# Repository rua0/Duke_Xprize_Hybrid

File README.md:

# Duke_Xprize_Hybrid
Codes and documents for a hybrid-electrical system used for Duke Ocean Xprize entry

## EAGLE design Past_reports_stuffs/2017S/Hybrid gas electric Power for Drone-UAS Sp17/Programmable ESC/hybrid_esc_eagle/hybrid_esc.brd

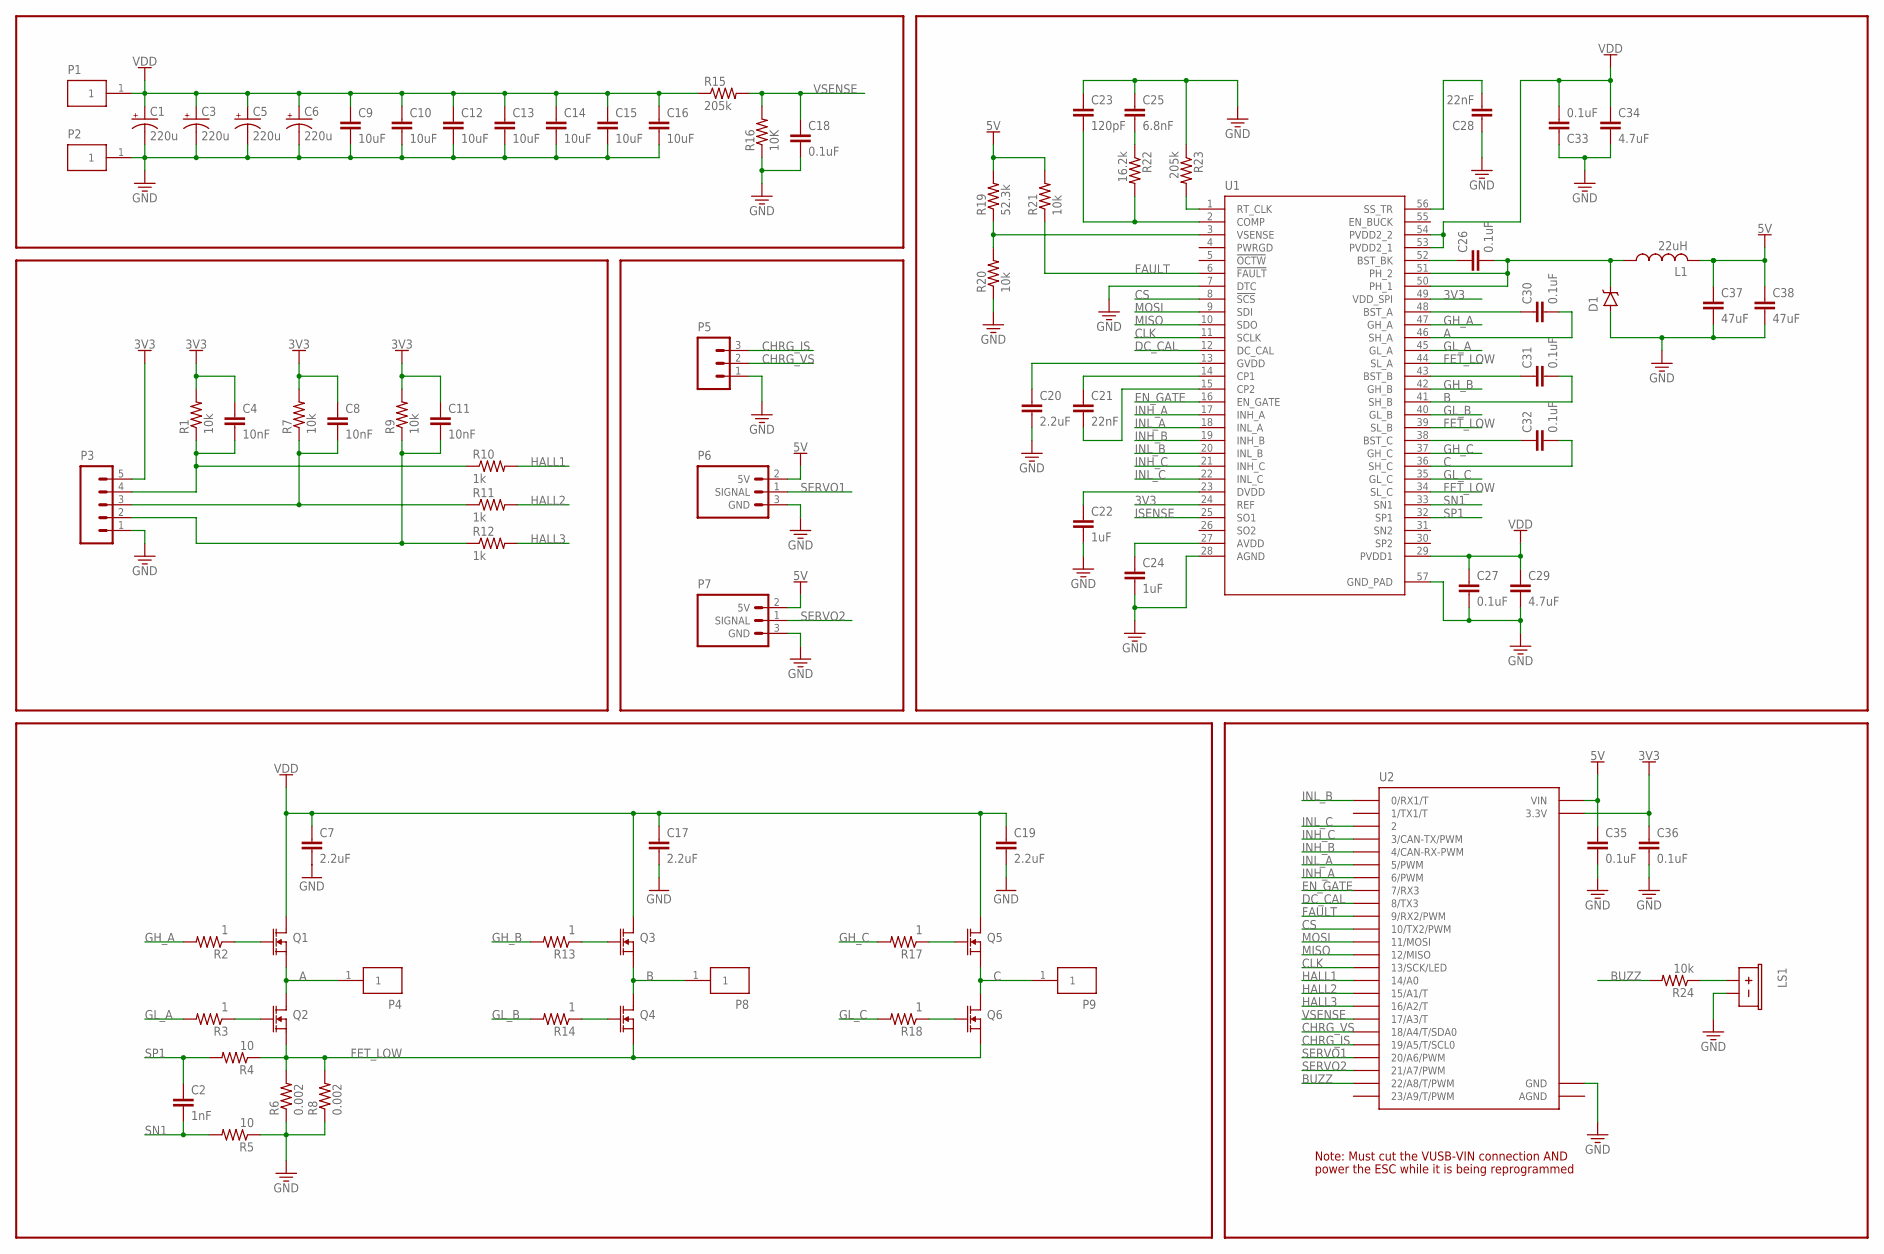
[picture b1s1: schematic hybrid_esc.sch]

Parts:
C1, C3, C5, C6: 220u; CPOL_10_5
C2: 1nF; C0603
C4, C8, C11: 10nF; C0603
C7, C17, C19: 2.2uF; C1206
C9, C10, C12, C13, C14, C15, C16: 10uF; C1206
C18, C26, C27, C30, C31, C32, C33, C35, C36: 0.1uF; C0603
C20: 2.2uF; C0603
C21, C28: 22nF; C0603
C22, C24: 1uF; C0603
C23: 120pF; C0603
C25: 6.8nF; C0603
C29, C34: 4.7uF; C1206
C37, C38: 47uF; C1206
D1: D_SOD123W; SOD123W
L1: 22uH; SDR0805
LS1: BUZZER_12MM
P1, P2, P4, P8, P9: POWER_PAD
P3: JST-XH5
P5: CONN_03
P6, P7: SERVO
Q1, Q2, Q3, Q4, Q5, Q6: NFET_D2PAK-7; D2PAK-7
R1, R7, R9, R20, R21, R24: 10k; R0603
R2, R3, R13, R14, R17, R18: 1; R0603
R4, R5: 10; R0603
R6, R8: 0.002; R2512
R10, R11, R12: 1k; R0603
R15, R23: 205k; R0603
R16: 10K; R0603
R19: 52.3k; R0603
R22: 16.2k; R0603
U1: DRV8301; TSSOP56P
U2: TEENSY_3.1

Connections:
3V3: C4.1, C8.1, C11.1, C36.1, P3.5, R1.2, R7.2, R9.2, U1.24 (REF), U1.49 (VDD_SPI), U2.3.3V
5V: C35.1, C37.1, C38.1, L1.2, P6.2 (5V), P7.2 (5V), R19.2, R21.2, U2.VIN
A: C30.2, P4.1, Q1.S, Q1.S1 (S), Q1.S2 (S), Q1.S3 (S), Q1.S4 (S), Q2.D, U1.46 (SH_A)
AGND: U2.AGND
B: C31.2, P8.1, Q3.S, Q3.S1 (S), Q3.S2 (S), Q3.S3 (S), Q3.S4 (S), Q4.D, U1.41 (SH_B)
BUZZ: R24.2, U2.22/A8 (22/A8/T/PWM)
C: C32.2, P9.1, Q5.S, Q5.S1 (S), Q5.S2 (S), Q5.S3 (S), Q5.S4 (S), Q6.D, U1.36 (SH_C)
CHRG_IS: P5.3, U2.19/A5 (19/A5/T/SCL0)
CHRG_VS: P5.2, U2.18/A4 (18/A4/T/SDA0)
CLK: U1.11 (SCLK), U2.13 (13/SCK/LED)
CS: U1.8 (!SCS), U2.10 (10/TX2/PWM)
DC_CAL: U1.12 (DC_CAL), U2.8 (8/TX3)
EN_GATE: U1.16 (EN_GATE), U2.7 (7/RX3)
FAULT: R21.1, U1.6 (!FAULT), U2.9 (9/RX2/PWM)
FET_LOW: Q2.S, Q2.S1 (S), Q2.S2 (S), Q2.S3 (S), Q2.S4 (S), Q4.S, Q4.S1 (S), Q4.S2 (S), Q4.S3 (S), Q4.S4 (S), Q6.S, Q6.S1 (S), Q6.S2 (S), Q6.S3 (S), Q6.S4 (S), R4.1, R6.2, R8.2, U1.34 (SL_C), U1.39 (SL_B), U1.44 (SL_A)
GH_A: R2.2, U1.47 (GH_A)
GH_B: R13.2, U1.42 (GH_B)
GH_C: R17.2, U1.37 (GH_C)
GL_A: R3.2, U1.45 (GL_A)
GL_A': Q2.G, R3.1
GL_B: R14.2, U1.40 (GL_B)
GL_B': Q4.G, R14.1
GL_C: R18.2, U1.35 (GL_C)
GL_C': Q6.G, R18.1
GND: C1.-, C3.-, C5.-, C6.-, C7.2, C9.2, C10.2, C12.2, C13.2, C14.2, C15.2, C16.2, C17.2, C18.2, C19.2, C20.2, C22.2, C23.1, C24.2, C25.1, C27.2, C28.1, C29.2, C33.1, C34.2, C35.2, C36.2, C37.2, C38.2, D1.A, LS1.-, P2.1, P3.1, P5.1, P6.3 (GND), P7.3 (GND), R5.1, R6.1, R8.1, R16.1, R20.1, R23.1, U1.7 (DTC), U1.28 (AGND), U1.57 (GND_PAD), U2.GND
HALL1: R10.2, U2.14/A0
HALL2: R11.2, U2.15/A1 (15/A1/T)
HALL3: R12.2, U2.16/A2 (16/A2/T)
INH_A: U1.17 (INH_A), U2.6 (6/PWM)
INH_B: U1.19 (INH_B), U2.4 (4/CAN-RX-PWM)
INH_C: U1.21 (INH_C), U2.3 (3/CAN-TX/PWM)
INL_A: U1.18 (INL_A), U2.5 (5/PWM)
INL_B: U1.20 (INL_B), U2.0 (0/RX1/T)
INL_C: U1.22 (INL_C), U2.2
ISENSE: U1.25 (SO1)
MISO: U1.10 (SDO), U2.12 (12/MISO)
MOSI: U1.9 (SDI), U2.11 (11/MOSI)
unnamed: Q3.G, R13.1
unnamed: R19.1, R20.2, U1.3 (VSENSE)
unnamed: C23.2, R22.2, U1.2 (COMP)
unnamed: C22.1, U1.23 (DVDD)
unnamed: Q5.G, R17.1
unnamed: C28.2, U1.56 (SS_TR)
unnamed: C25.2, R22.1
unnamed: C26.1, U1.52 (BST_BK)
unnamed: Q1.G, R2.1
unnamed: R23.2, U1.1 (RT_CLK)
unnamed: C4.2, P3.4, R1.1, R10.1
unnamed: LS1.+, R24.1
unnamed: C8.2, P3.3, R7.1, R11.1
unnamed: C11.2, P3.2, R9.1, R12.1
unnamed: C32.1, U1.38 (BST_C)
unnamed: C21.1, U1.14 (CP1)
unnamed: C24.1, U1.27 (AVDD)
unnamed: C21.2, U1.15 (CP2)
unnamed: C20.1, U1.13 (GVDD)
unnamed: C31.1, U1.43 (BST_B)
unnamed: C30.1, U1.48 (BST_A)
unnamed: C26.2, D1.C, L1.1, U1.50 (PH_1), U1.51 (PH_2)
SERVO1: P6.1 (SIGNAL), U2.20/A6 (20/A6/PWM)
SERVO2: P7.1 (SIGNAL), U2.21/A7 (21/A7/PWM)
SN1: C2.2, R5.2, U1.33 (SN1)
SP1: C2.1, R4.2, U1.32 (SP1)
VDD: C1.+, C3.+, C5.+, C6.+, C7.1, C9.1, C10.1, C12.1, C13.1, C14.1, C15.1, C16.1, C17.1, C19.1, C27.1, C29.1, C33.2, C34.1, P1.1, Q1.D, Q3.D, Q5.D, R15.1, U1.29 (PVDD1), U1.53 (PVDD2_1), U1.54 (PVDD2_2)
VSENSE: C18.1, R15.2, R16.2, U2.17/A3 (17/A3/T)

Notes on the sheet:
Note: Must cut the VUSB-VIN connection AND
power the ESC while it is being reprogrammed

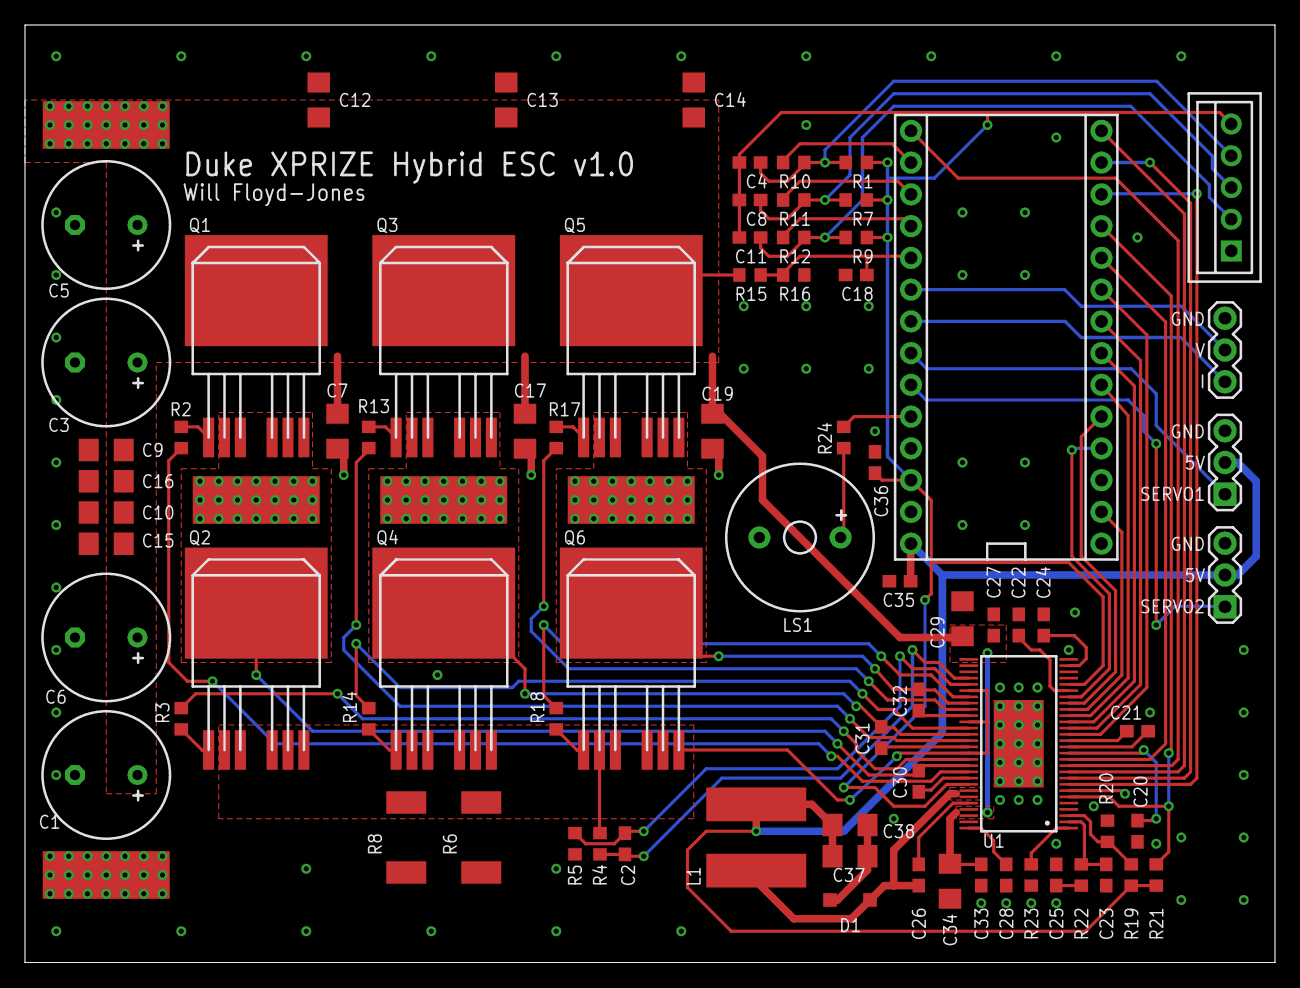
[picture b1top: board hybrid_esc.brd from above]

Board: 2 copper layers, 100.0 x 75.0 mm, 82 parts (0 on the bottom side), 63 nets.

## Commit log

2018-06-21 Initial Upload
    Code base. Tuning needed
2018-06-22 Tests to tune throttle position
    min is 285 ticks, wide open;
    max is 340 ticks, closed
2018-06-22 Tuned upper tick bound for throttle
    Changed max pulse length param for throttle and made upper tick bound 350 (obtained by experiment)
2018-06-22 Tuned for servos
    Tuned for parameters on throttle and choke servos
2018-06-22 ESC Tuning
2018-06-27 Change sequence instructions
    Changed instructions for different sequences. Hopefully it works for test today
2018-06-27 Tuning
2018-06-27 Tuning
    Changed ESC PL min.
    11 percent to start from no movement
2018-07-02 Worked
2018-07-11 Engine docs
2018-07-30 Current sensor
2018-08-06 Object-oriented
    made and encapsulated engine object
2018-08-25 names and contact
